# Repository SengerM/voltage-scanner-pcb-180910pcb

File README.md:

# voltage-scanner-pcb-180910pcb

[KiCad](http://kicad-pcb.org/) project for the 180919PCB board. This board handles the system for checking the line status. The schematic of this board can be found in [this link](export/180919PCB.pdf). Below is the layout.

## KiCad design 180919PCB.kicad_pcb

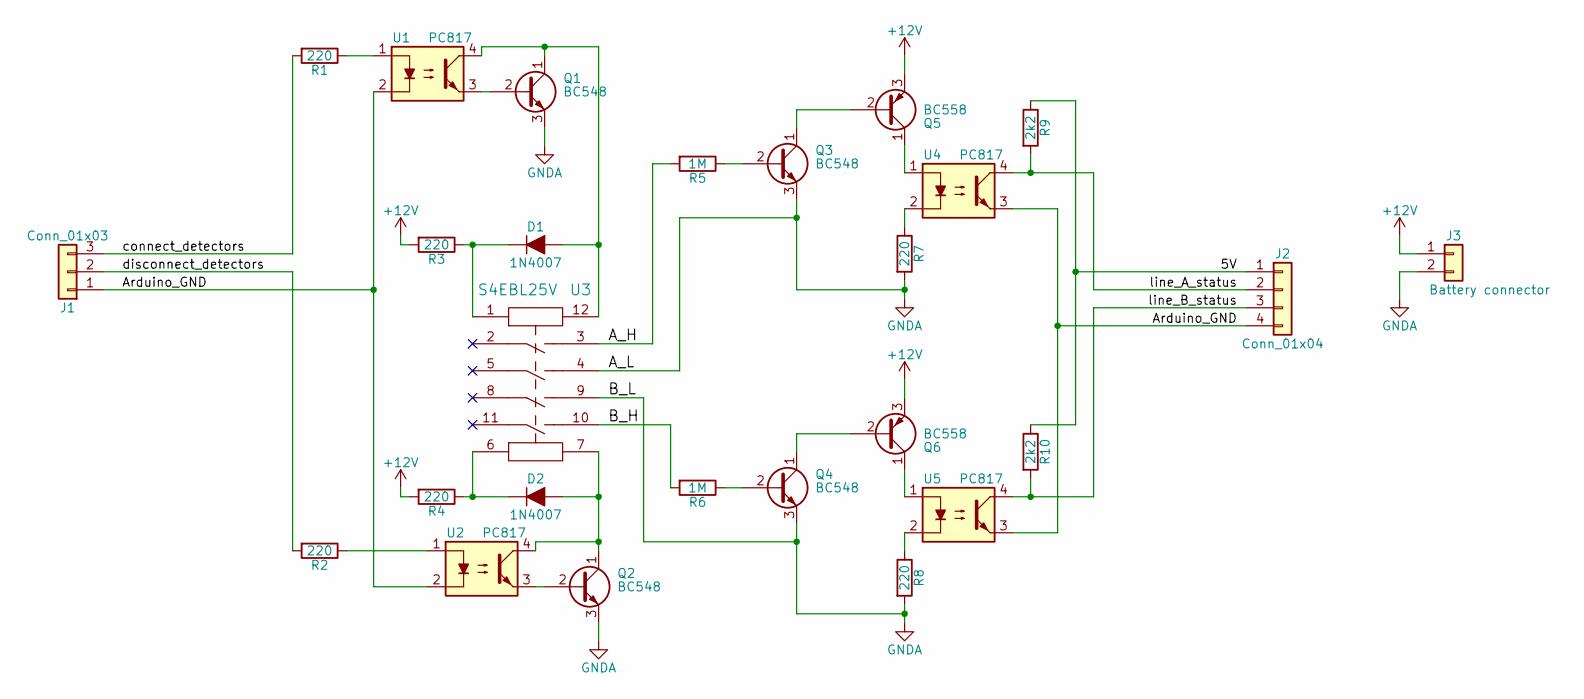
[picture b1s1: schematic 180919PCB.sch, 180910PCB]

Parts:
D1, D2: 1N4007; D_SMA-SMB_Universal_Handsoldering
J1: Conn_01x03; Pin_Header_Straight_1x03_Pitch2.54mm
J2: Conn_01x04; Pin_Header_Straight_1x04_Pitch2.54mm
J3: Battery connector; Pin_Header_Straight_2x01_Pitch2.54mm
Q1, Q2, Q3, Q4: BC548; TO-92_Molded_Narrow_CUSTOM_PADS
Q5, Q6: BC558; TO-92_Molded_Narrow_CUSTOM_PADS
R1, R2, R3, R4, R7, R8: 220; R_1206
R5, R6: 1M; R_1206
R9, R10: 2k2; R_1206
U1, U2, U4, U5: PC817; DIP-4_W7.62mm
U3: S4EBL25V

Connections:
+12V: J3.1, Q5.3 (E), Q6.3 (E), R3.2, R4.2
/5V: J2.1, R9.1, R10.1
/A_H: R5.2, U3.3
/Arduino_GND: J1.1, J2.4, U1.2, U2.2, U4.3, U5.3
/B_H: R6.2, U3.10
/connect_detectors: J1.3, R1.2
/disconnect_detectors: J1.2, R2.2
/line_A_status: J2.2, R9.2, U4.4
/line_B_status: J2.3, R10.2, U5.4
GNDA: J3.2, Q1.3 (E), Q2.3 (E), Q3.3 (E), Q4.3 (E), R7.2, R8.2, U3.4, U3.9
unnamed: D1.1 (K), R3.1, U3.1
unnamed: D1.2 (A), Q1.1 (C), U1.4, U3.12
unnamed: D2.1 (K), R4.1, U3.6
unnamed: D2.2 (A), Q2.1 (C), U2.4, U3.7
unnamed: Q1.2 (B), U1.3
unnamed: Q2.2 (B), U2.3
unnamed: Q3.1 (C), Q5.2 (B)
unnamed: Q3.2 (B), R5.1
unnamed: Q4.1 (C), Q6.2 (B)
unnamed: Q4.2 (B), R6.1
unnamed: Q5.1 (C), U4.1
unnamed: Q6.1 (C), U5.1
unnamed: R1.1, U1.1
unnamed: R2.1, U2.1
unnamed: R7.1, U4.2
unnamed: R8.1, U5.2

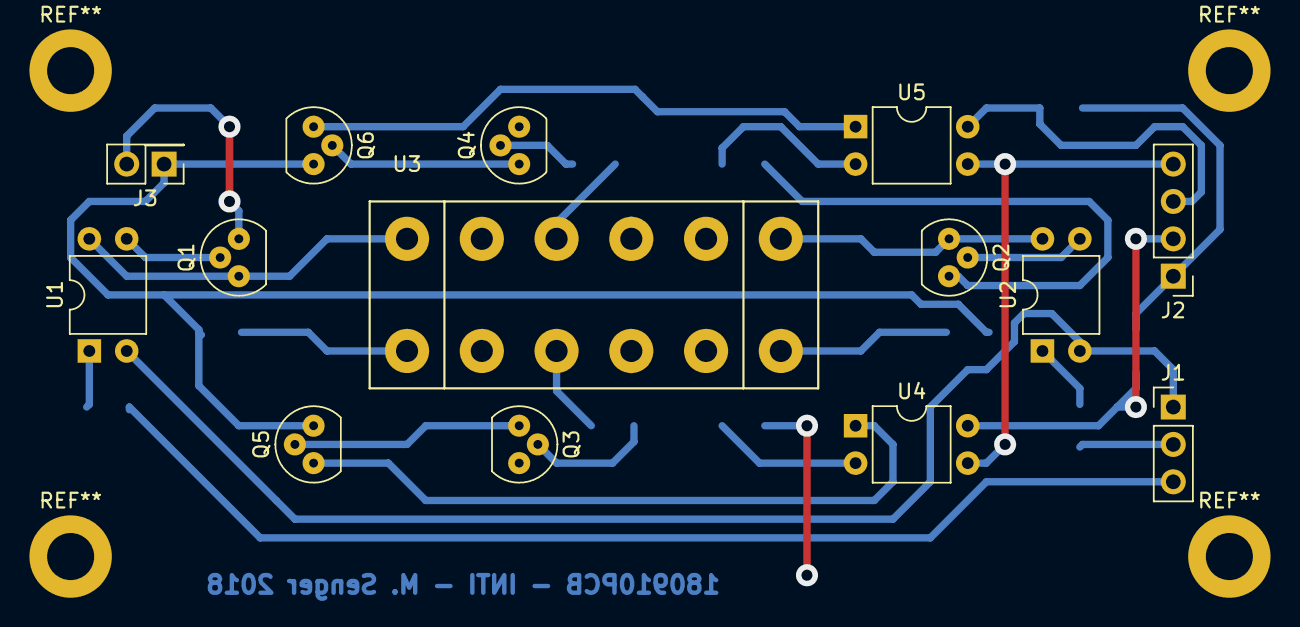
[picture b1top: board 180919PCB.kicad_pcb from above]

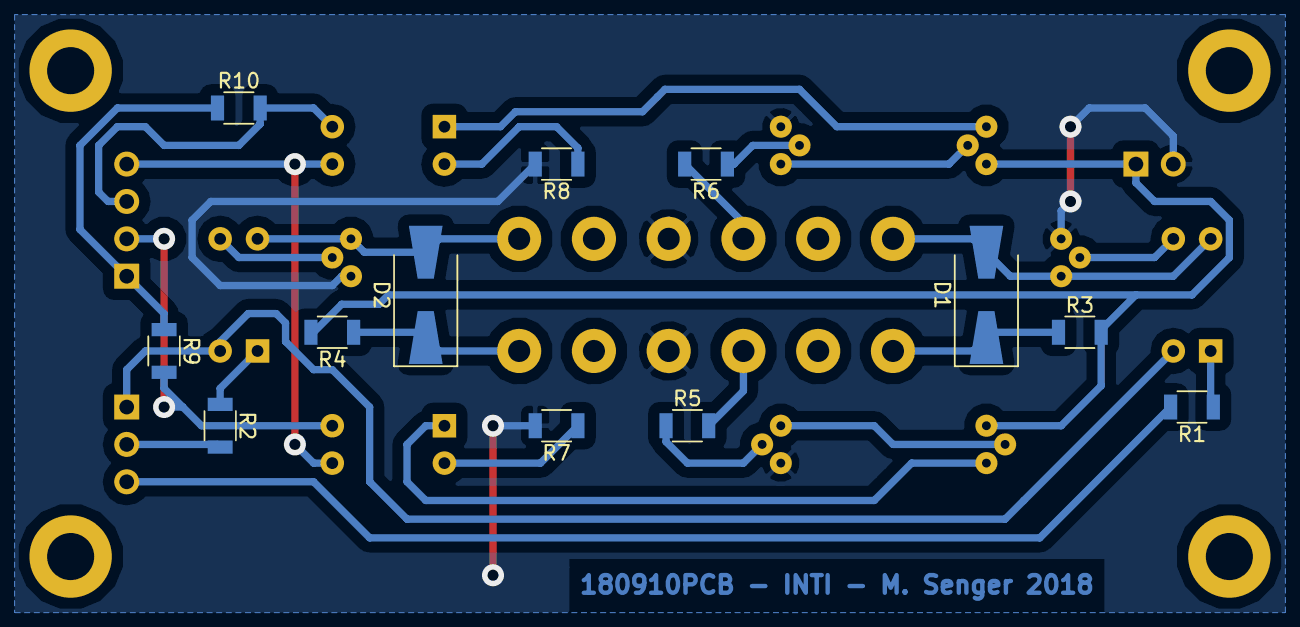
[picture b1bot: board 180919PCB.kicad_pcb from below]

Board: 2 copper layers, 26 parts (12 on the bottom side), 26 nets.
